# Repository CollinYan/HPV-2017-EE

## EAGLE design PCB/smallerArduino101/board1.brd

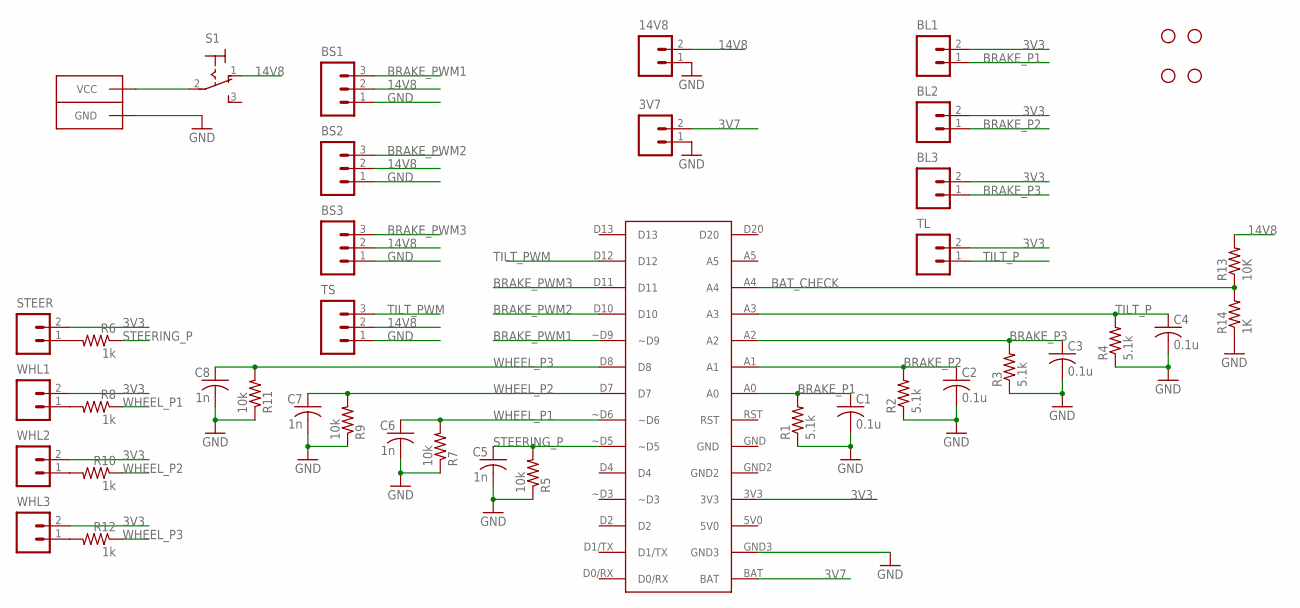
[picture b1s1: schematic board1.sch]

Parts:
3V7, 14V8: M02PTH; 1X02
BL1, BL2, BL3: M02PTH; 1X02
BS1, BS2, BS3: M03PTH; 1X03
C1, C2, C3, C4: 0.1u; C0603
C5, C6, C7, C8: 1n; C0603
JP13, JP14, JP15, JP16: STAND-OFF
LIPO: ANDERSONHORIZONTAL; ANDERSON_HORIZONTAL
R1, R2, R3, R4: 5.1k; R0603
R5, R7, R9, R11: 10k; R0603
R6, R8, R10, R12: 1k; R0603
R13: 10K; R0603
R14: 1K; R0603
S1: M9040P
STEER: M02PTH; 1X02
TL: M02PTH; 1X02
TS: M03PTH; 1X03
U$1: CURIENANO_BREAKOUT; CURIENANO
WHL1, WHL2, WHL3: M02PTH; 1X02

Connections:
3V3: BL1.2, BL2.2, BL3.2, STEER.2, TL.2, U$1.3V3, WHL1.2, WHL2.2, WHL3.2
3V7: 3V7.2, U$1.BAT
14V8: 14V8.2, BS1.2, BS2.2, BS3.2, R13.2, S1.1 (O), TS.2
BAT_CHECK: R13.1, R14.2, U$1.A4
BRAKE_P1: BL1.1, C1.1, R1.2, U$1.A0
BRAKE_P2: BL2.1, C2.1, R2.2, U$1.A1
BRAKE_P3: BL3.1, C3.1, R3.2, U$1.A2
BRAKE_PWM1: BS1.3, U$1.~D9
BRAKE_PWM2: BS2.3, U$1.D10
BRAKE_PWM3: BS3.3, U$1.D11
GND: 3V7.1, 14V8.1, BS1.1, BS2.1, BS3.1, C1.2, C2.2, C3.2, C4.2, C5.2, C6.2, C7.2, C8.2, LIPO.PIN1 (GND), LIPO.PIN1-LEAD (GND), R1.1, R2.1, R3.1, R4.1, R5.1, R7.1, R9.1, R11.1, R14.1, TS.1, U$1.GND3
unnamed: R6.2, STEER.1
unnamed: R8.2, WHL1.1
unnamed: R10.2, WHL2.1
unnamed: R12.2, WHL3.1
unnamed: LIPO.PIN2 (VCC), LIPO.PIN2-LEAD (VCC), S1.2
STEERING_P: C5.1, R5.2, R6.1, U$1.~D5
TILT_P: C4.1, R4.2, TL.1, U$1.A3
TILT_PWM: TS.3, U$1.D12
WHEEL_P1: C6.1, R7.2, R8.1, U$1.~D6
WHEEL_P2: C7.1, R9.2, R10.1, U$1.D7
WHEEL_P3: C8.1, R11.2, R12.1, U$1.D8

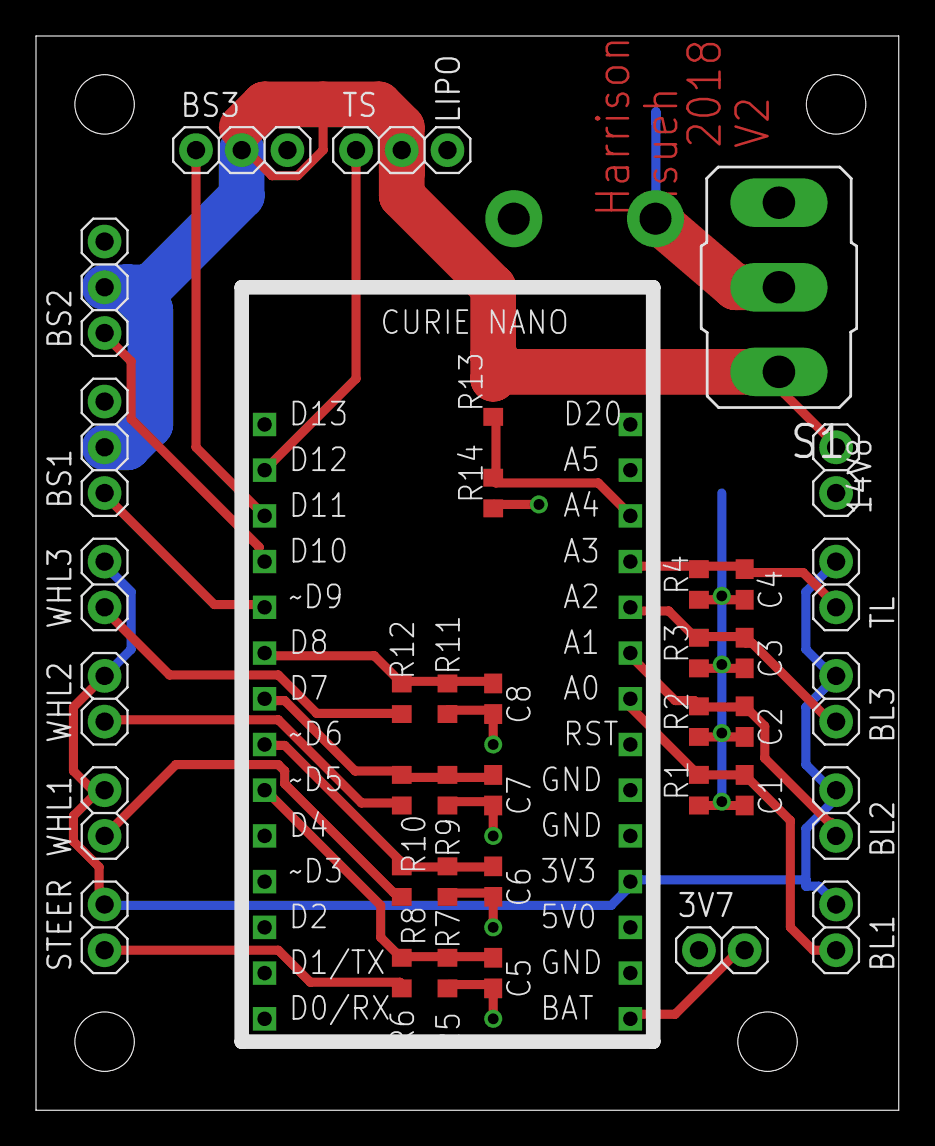
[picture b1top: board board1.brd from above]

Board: 2 copper layers, 47.9 x 59.7 mm, 43 parts (1 on the bottom side), 22 nets.

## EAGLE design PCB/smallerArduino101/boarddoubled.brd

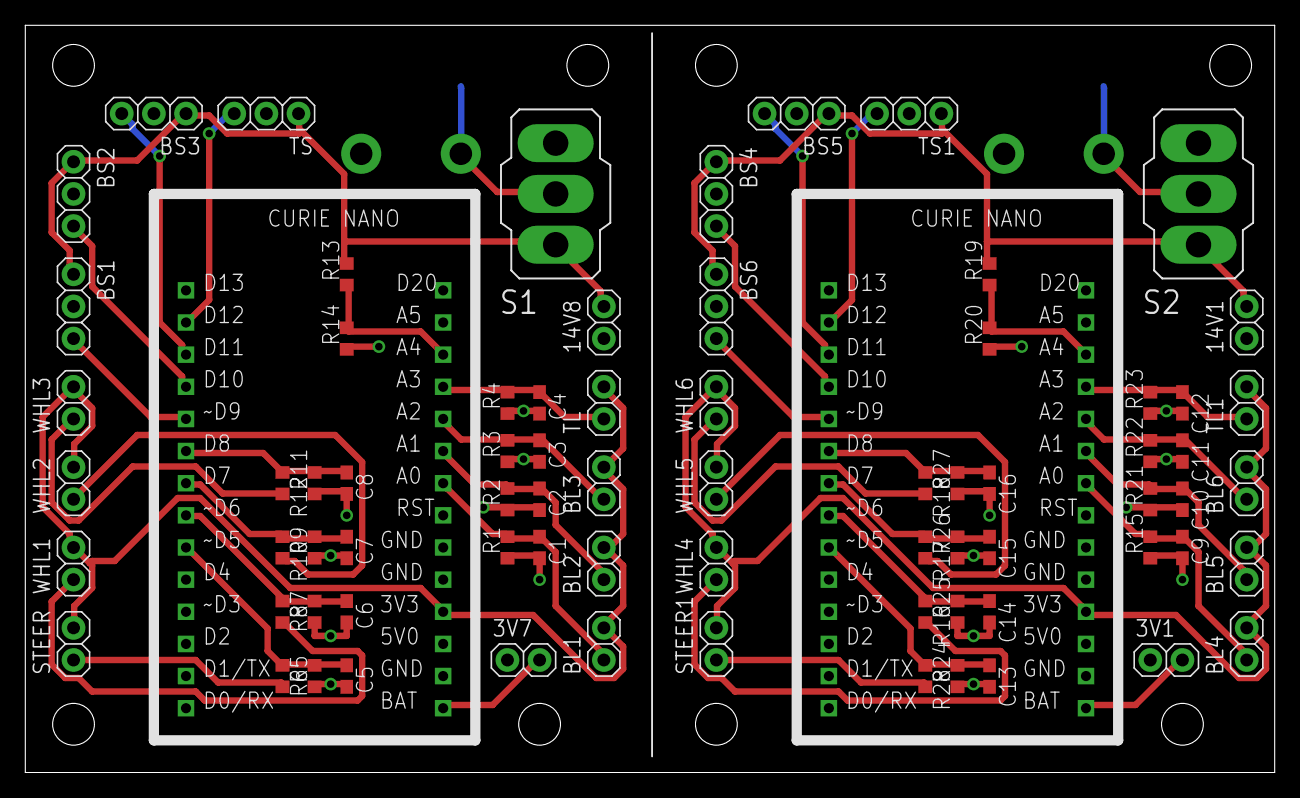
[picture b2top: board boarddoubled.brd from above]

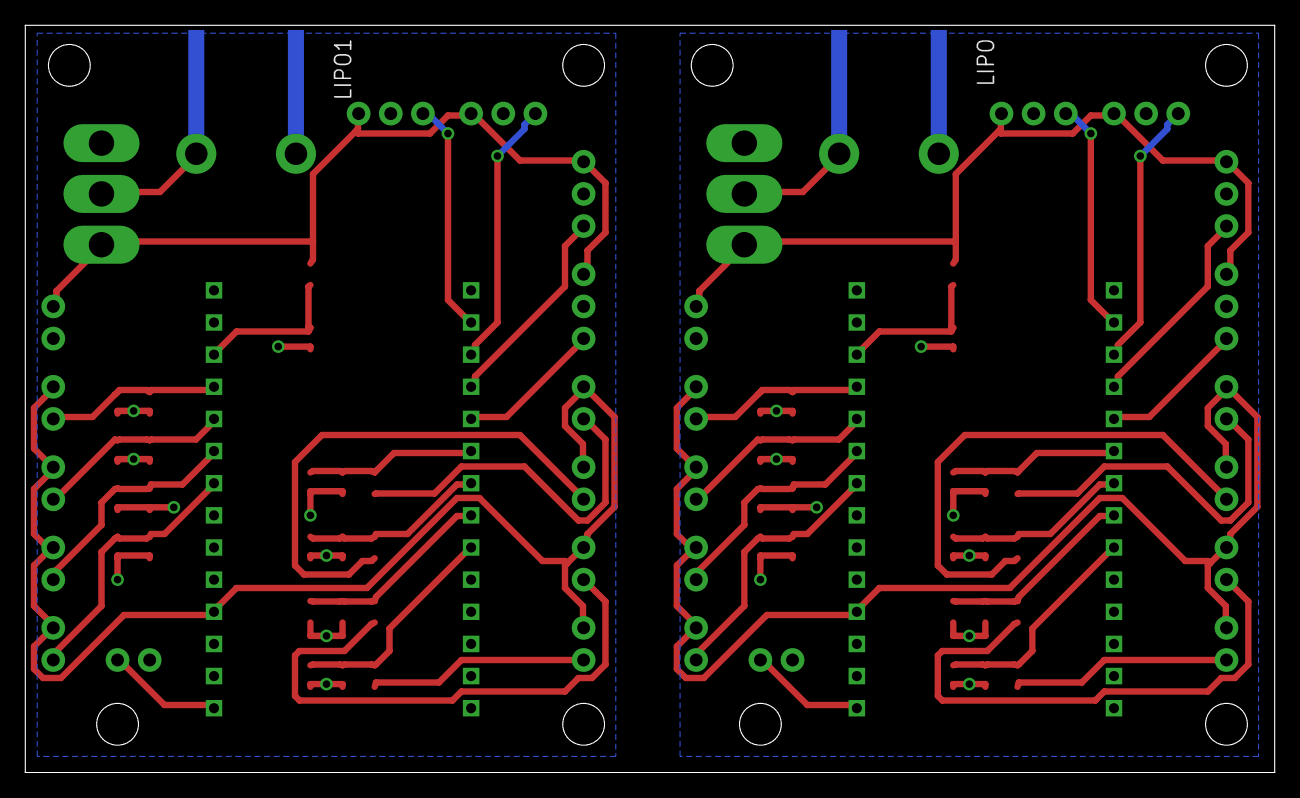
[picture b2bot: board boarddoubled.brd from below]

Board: 2 copper layers, 98.7 x 59.0 mm, 86 parts (2 on the bottom side), 44 nets.

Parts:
3V1, 3V7, 14V1, 14V8: 1X02
BL1, BL2, BL3, BL4, BL5, BL6: 1X02
BS1, BS2, BS3, BS4, BS5, BS6: 1X03
C1, C2, C3, C4, C9, C10, C11, C12: 0.1u; C0603
C5, C6, C7, C8, C13, C14, C15, C16: 1n; C0603
JP1, JP2, JP3, JP4, JP13, JP14, JP15, JP16: STAND-OFF
LIPO, LIPO1: ANDERSONHORIZONTAL; ANDERSON_HORIZONTAL
R1, R2, R3, R4, R15, R21, R22, R23: 5.1k; R0603
R5, R7, R9, R11, R24, R25, R26, R27: 10k; R0603
R6, R8, R10, R12, R16, R17, R18, R28: 1k; R0603
R13, R19: 10K; R0603
R14, R20: 1K; R0603
S1, S2: 320-916
STEER, STEER1: 1X02
TL, TL1: 1X02
TS, TS1: 1X03
U$1, U$2: CURIENANO_BREAKOUT; CURIENANO
WHL1, WHL2, WHL3, WHL4, WHL5, WHL6: 1X02

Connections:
3V1: 3V1.2, U$2.BAT
3V2: BL4.2, BL5.2, BL6.2, STEER1.2, TL1.2, U$2.3V3, WHL4.2, WHL5.2, WHL6.2
3V3: BL1.2, BL2.2, BL3.2, STEER.2, TL.2, U$1.3V3, WHL1.2, WHL2.2, WHL3.2
3V7: 3V7.2, U$1.BAT
14V1: 14V1.2, BS4.1, BS5.1, BS6.1, R19.2, S2.1, TS1.1
14V8: 14V8.2, BS1.1, BS2.1, BS3.1, R13.2, S1.1, TS.1
BAT_CHECK: R13.1, R14.2, U$1.A4
BAT_CHECK1: R19.1, R20.2, U$2.A4
BRAKE_P1: BL1.1, C1.1, R1.2, U$1.A0
BRAKE_P2: BL2.1, C2.1, R2.2, U$1.A1
BRAKE_P3: BL3.1, C3.1, R3.2, U$1.A2
BRAKE_P4: BL4.1, C9.1, R15.2, U$2.A0
BRAKE_P5: BL5.1, C10.1, R21.2, U$2.A1
BRAKE_P6: BL6.1, C11.1, R22.2, U$2.A2
BRAKE_PWM1: BS1.3, U$1.~D9
BRAKE_PWM2: BS2.3, U$1.D10
BRAKE_PWM3: BS3.3, U$1.D11
BRAKE_PWM4: BS5.3, U$2.D11
BRAKE_PWM5: BS4.3, U$2.D10
BRAKE_PWM6: BS6.3, U$2.~D9
GND: 3V7.1, 14V8.1, BS1.2, BS2.2, BS3.2, C1.2, C2.2, C3.2, C4.2, C5.2, C6.2, C7.2, C8.2, LIPO.PIN1, LIPO.PIN1-LEAD, R1.1, R2.1, R3.1, R4.1, R5.1, R7.1, R9.1, R11.1, R14.1, TS.2, U$1.GND3
GND1: 3V1.1, 14V1.1, BS4.2, BS5.2, BS6.2, C9.2, C10.2, C11.2, C12.2, C13.2, C14.2, C15.2, C16.2, LIPO1.PIN1, LIPO1.PIN1-LEAD, R15.1, R20.1, R21.1, R22.1, R23.1, R24.1, R25.1, R26.1, R27.1, TS1.2, U$2.GND3
unnamed: R6.2, STEER.1
unnamed: R8.2, WHL1.1
unnamed: R10.2, WHL2.1
unnamed: R12.2, WHL3.1
unnamed: LIPO.PIN2, LIPO.PIN2-LEAD, S1.2
unnamed: R28.2, STEER1.1
unnamed: R16.2, WHL4.1
unnamed: R17.2, WHL5.1
unnamed: R18.2, WHL6.1
unnamed: LIPO1.PIN2, LIPO1.PIN2-LEAD, S2.2
STEERING_P: C5.1, R5.2, R6.1, U$1.~D5
STEERING_P1: C13.1, R24.2, R28.1, U$2.~D5
TILT_P: C4.1, R4.2, TL.1, U$1.A3
TILT_P1: C12.1, R23.2, TL1.1, U$2.A3
TILT_PWM: TS.3, U$1.D12
TILT_PWM1: TS1.3, U$2.D12
WHEEL_P1: C6.1, R7.2, R8.1, U$1.~D6
WHEEL_P2: C7.1, R9.2, R10.1, U$1.D7
WHEEL_P3: C8.1, R11.2, R12.1, U$1.D8
WHEEL_P4: C16.1, R18.1, R27.2, U$2.D8
WHEEL_P5: C15.1, R17.1, R26.2, U$2.D7
WHEEL_P6: C14.1, R16.1, R25.2, U$2.~D6

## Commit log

2018-01-30 collin is the best
2018-02-03 Added first draft of auto lock feature
2018-02-03 Added auto tilt lock and brake servo outputs
2018-02-03 block diagram, comments in cotnroler
2018-02-03 added servo.h and a couple lines
2018-02-03 arduino ide asked me to save...
2018-02-03 fixed convertToServo func int/double issue
2018-02-04 added serial print statements
2018-02-04 rough draft array class & changed ranges in controller/func
2018-02-06 change pins and variable names for brake and tilt and added block diagram docx
2018-02-06 added constraint to servo angle to protect it
2018-02-06 added tiltServo object and changed mapping function
2018-02-09 moved array deque out of controller since it didnt compile, added smoothing and actualy servo values for current setup, need to make smoothing a library instead
2018-02-09 added smoothing library for integer input but float output and also oragnized tilt lock code
2018-02-09 accidentayll deleted the actual unlocking mechanism, readded with min value as reference
2018-02-09 changed for larger window for noise and made smoothing actualy return a float
2018-02-09 increased smoothing to 10 samples so 50ms, but still very noisy, need to fix noise either hardware or more software averagin, also locks onto 75 when minimum is 70, causing excess power draw since it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
2018-02-09 increase sampling freq so we can smooth more values but we should decrease actuation frequency back to around 200hz later. also implemented quick fix for locking into minimum position as it was locki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
2018-02-12 updated locking to lock to current position instead of lock-4, both should save batttery. also decreased frequency and averaging count since we made the hardware have higher resolution
2018-02-16 updated code for nonlinear response
2018-02-16 changed nonlinearity
2018-02-20 making library for locking
2018-02-20 finished locknig librayr and tested
2018-02-20 cleaned up controller code and increased smoothing to 5 samples which corresponds to 50ms
2018-02-20 typos in last commit and adding condition for checking magnets
2018-02-20 setting up 1khz interrupt for wheel speed
2018-02-21 pcb for arduino curienano breakout
2018-02-22 schematic v1 and layed out components
2018-02-22 autorouted
2018-02-22 laayed out smaller 0603 pakcages, need to smash values
2018-02-22 smashed values
2018-02-22 renamed jumpers and connectors
2018-02-22 added buck converter
2018-02-22 removed deleted files on my end
2018-02-22 finshed routing, made a board with duplicate, need to check anderson
2018-02-22 submitted ersion of gerber to bac
2018-02-23 cleaned up wheelspeed code to compile for curienano but will next get ride of debounce and useless stuff
2018-02-23 organized wheelspeed and no debounce
2018-02-24 changed wheelspeed to use external interrupts, stil l with rising and falilng edge, will changed to rising only
2018-02-24 cleaned up accelSpeed and edited some structure in controler to impelment wheel and accel speed and abs
2018-02-24 made copy of controller to keep easy access of manual braking
2018-02-26 excel for wheel speed error calcs, and changed brake freq to 20hz
2018-02-27 tested wheelspeed, added debounce
2018-02-27 working prototype version testing on bike
2018-02-27 reduced code in wheel interrupt and updates, need to test speed
2018-02-27 added timgin code for wheelseped and controller
2018-02-28 changed condition for reading brake lever so doesnt have to be exaclt at the ms
2018-02-28 wheelspeed constant has issue giving 0mph, breaking working at speed now
2018-02-28 made copy into controller, ready for accel and pid
2018-03-01 changed units issues with wheelspeed mph and added calibrationg when initializing accelerometer
2018-03-01 updated wheelspeed library
2018-03-02 deleted unneede variable in accelspeed freom testing
2018-03-02 fixed compil erros in wheelspeed
2018-03-02 moved AccelSpeed to libraries
2018-03-02 wheelspeed working
2018-03-02 implemented accelspeed into controller
2018-03-02 changed unit issues, got data, need to add accel compensation constant
2018-03-03 added fixaround for accel, added p contorller
2018-03-03 accelSpeed now calc'd from downscaled accel & converted to 100 mi / h
2018-03-03 fixed accelspeed unit conversion & renamed vehicleSpeed to mphX100
2018-03-04 updated wheelspeed to calc mphX100 instead of mphX10
2018-03-04 controlerl codee all mphX100
2018-03-04 copied wheelspeed folder into library
2018-03-04 fixed AccelSpeed constructor, int/float freq
2018-03-04 moved AccelSpeed to library
2018-03-04 fixed wheelspeed scaling
2018-03-04 wheelspeed redo scaling
2018-03-04 was off by factor of ten for center space calc wheelspeed
2018-03-06 v2 pcb, code for pid, data for pid on bike
2018-03-07 cleaned up code and pid
2018-03-07 changed from brakeServoOutput1 to brakeServoOutput2
2018-03-07 yolo
2018-03-07 trying to fix controller pid
2018-03-07 debugging pid with print, change manual and auto modes for pid when under speed lim
2018-03-08 pid workingbetter neeed to tune pi
2018-03-09 equal performance with skid
2018-03-09 changing forslip cond
2018-03-09 much better than manual
2018-03-09 file for less traces only vel matlab
2018-03-09 fixed accel sync code and compiled
2018-03-10 testing accel
2018-03-20 stuff used for innovation video
2018-03-21 created controller_comp
2018-03-21 super basci controller ocmp basic
